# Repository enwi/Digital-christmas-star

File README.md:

# Digital-christmas-star

## Videos

Special thanks to [PCBWay](https://www.pcbway.com/) for sponsoring the video!

## Parameters that need to be changed before upload
* DATA_PIN -> The IO pin to which the LED's are connnected
* NUM_FINS -> The number of fins (for a regular star 4-5)
* NUM_LEDS_BETWEEN_TIPS -> The number of LED's between the tips (not including tips)
* animationTime -> The time in milliseconds how long each animation is shown

## Adding new animations
* Add a new animation function
* Add a new case to the switch case
* Call the function in the created case
* Increase maxMode by 1 (set it to the same number as the last number of the switch case)

# Support
If you want to support my work you can store on Amazon via this link: [Amazon Referral Link](https://www.amazon.de/?tag=enwi-21). This is an affiliate link. Through a purchase via this link, I will participate in the turnover. This has no effect on the price for you.

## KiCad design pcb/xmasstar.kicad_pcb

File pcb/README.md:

# Schematic
To view the schematic just follow [this link](https://kicanvas.org/?github=https%3A%2F%2Fgithub.com%2Fenwi%2FDigital-christmas-star%2Ftree%2Fmaster%2Fpcb)

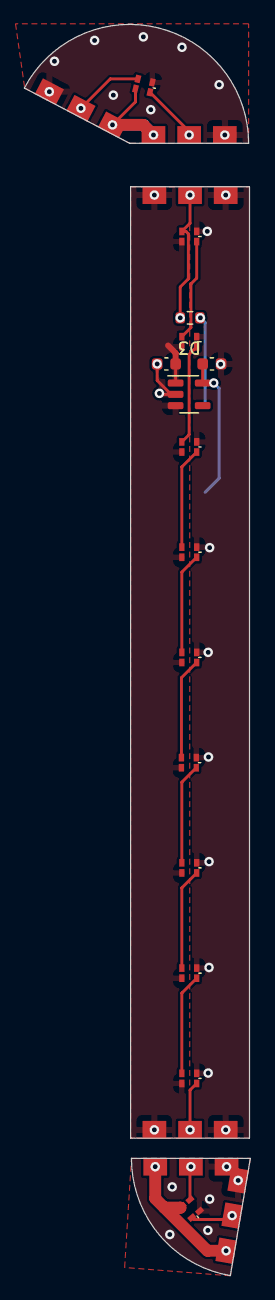
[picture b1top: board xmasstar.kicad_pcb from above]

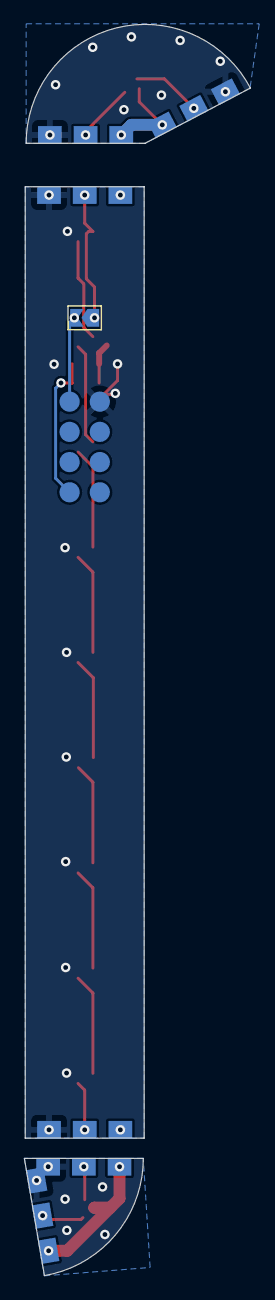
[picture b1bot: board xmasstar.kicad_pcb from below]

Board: 2 copper layers, 19.0 x 105.2 mm, 29 parts (8 on the bottom side), 18 nets.

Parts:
C1, C2: 1u; C_0603_1608Metric
D1, D2, D3, D4, D5, D6, D7, D8, D9, D10, D11: WS2812B; 1615RGBC
J1, J1#2, J2, J2#2, J4, J4#2, J5, J5#2, J6, J6#2, J7, J7#2: Conn_01x03; star_edge
J3: Conn_02x04_Odd_Even; 02x04_smd
JP1: SolderJumper_2_Open; SolderJumper-2_P1.3mm_Open_TrianglePad1.0x1.5mm
R1: 200; R_0603_1608Metric
U1: RT9167A-xxxB; TSOT-23-5

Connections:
+3V3: C2.1, J3.8, U1.5 (VOUT)
+5V: C1.1, D1.1 (VDD), D2.1 (VDD), D3.1 (VDD), D4.1 (VDD), D5.1 (VDD), D6.1 (VDD), D7.1 (VDD), D8.1 (VDD), D9.1 (VDD), D10.1 (VDD), D11.1 (VDD), J1.3, J1#2.3, J2.1, J2#2.1, J4.3, J4#2.3, J5.1, J5#2.1, J6.3, J6#2.3, J7.1, J7#2.1, U1.1 (VIN), U1.3 (EN)
DIN: D2.4 (DIN), J4.2, J4#2.2, JP1.1 (A), R1.2
GND: C1.2, C2.2, D1.3 (VSS), D2.3 (VSS), D3.3 (VSS), D4.3 (VSS), D5.3 (VSS), D6.3 (VSS), D7.3 (VSS), D8.3 (VSS), D9.3 (VSS), D10.3 (VSS), D11.3 (VSS), J1.1, J1#2.1, J2.3, J2#2.3, J3.1, J4.1, J4#2.1, J5.3, J5#2.3, J6.1, J6#2.1, J7.3, J7#2.3, U1.2 (GND)
unnamed: D1.4 (DIN), J1.2, J1#2.2
unnamed: D1.2 (DOUT), J2.2, J2#2.2
unnamed: D2.2 (DOUT), D3.4 (DIN)
unnamed: D3.2 (DOUT), D4.4 (DIN)
unnamed: D4.2 (DOUT), D5.4 (DIN)
unnamed: D5.2 (DOUT), D6.4 (DIN)
unnamed: D6.2 (DOUT), D7.4 (DIN)
unnamed: D7.2 (DOUT), D8.4 (DIN)
unnamed: D8.2 (DOUT), D9.4 (DIN)
unnamed: D9.2 (DOUT), D10.4 (DIN)
unnamed: D10.2 (DOUT), J5.2, J5#2.2
unnamed: D11.4 (DIN), J6.2, J6#2.2
unnamed: D11.2 (DOUT), J7.2, J7#2.2
TX: J3.2, JP1.2 (B), R1.1

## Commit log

2019-11-30 Add code
2019-12-02 Create README with simple instructions
2020-11-25 Add support section to README
2020-11-29 Add option to have a star without tip and pit LEDs
2020-12-06 Add new circle animation and remove duplicate code
2020-12-06 Fix spelling mistake in README
2020-12-06 Include forward function declarations for other compilers
    For platformio users
2020-12-06 Add forward function declaration for platformio compiler
2023-12-20 Add second video and embed videos
2024-04-17 Add gitignore fix code for new star
2024-04-17 Add pcb
2024-04-17 Move pcb files into pcb folder
2024-04-17 Move custom footprints into custom xmasstar library
2024-10-30 Add LED_OFFSET and refactor code
2024-10-30 Update code.ino
    Removed bugs in LED_OFFSET aplication
2024-10-30 Update code.ino
    Remove different color step between last and first led
